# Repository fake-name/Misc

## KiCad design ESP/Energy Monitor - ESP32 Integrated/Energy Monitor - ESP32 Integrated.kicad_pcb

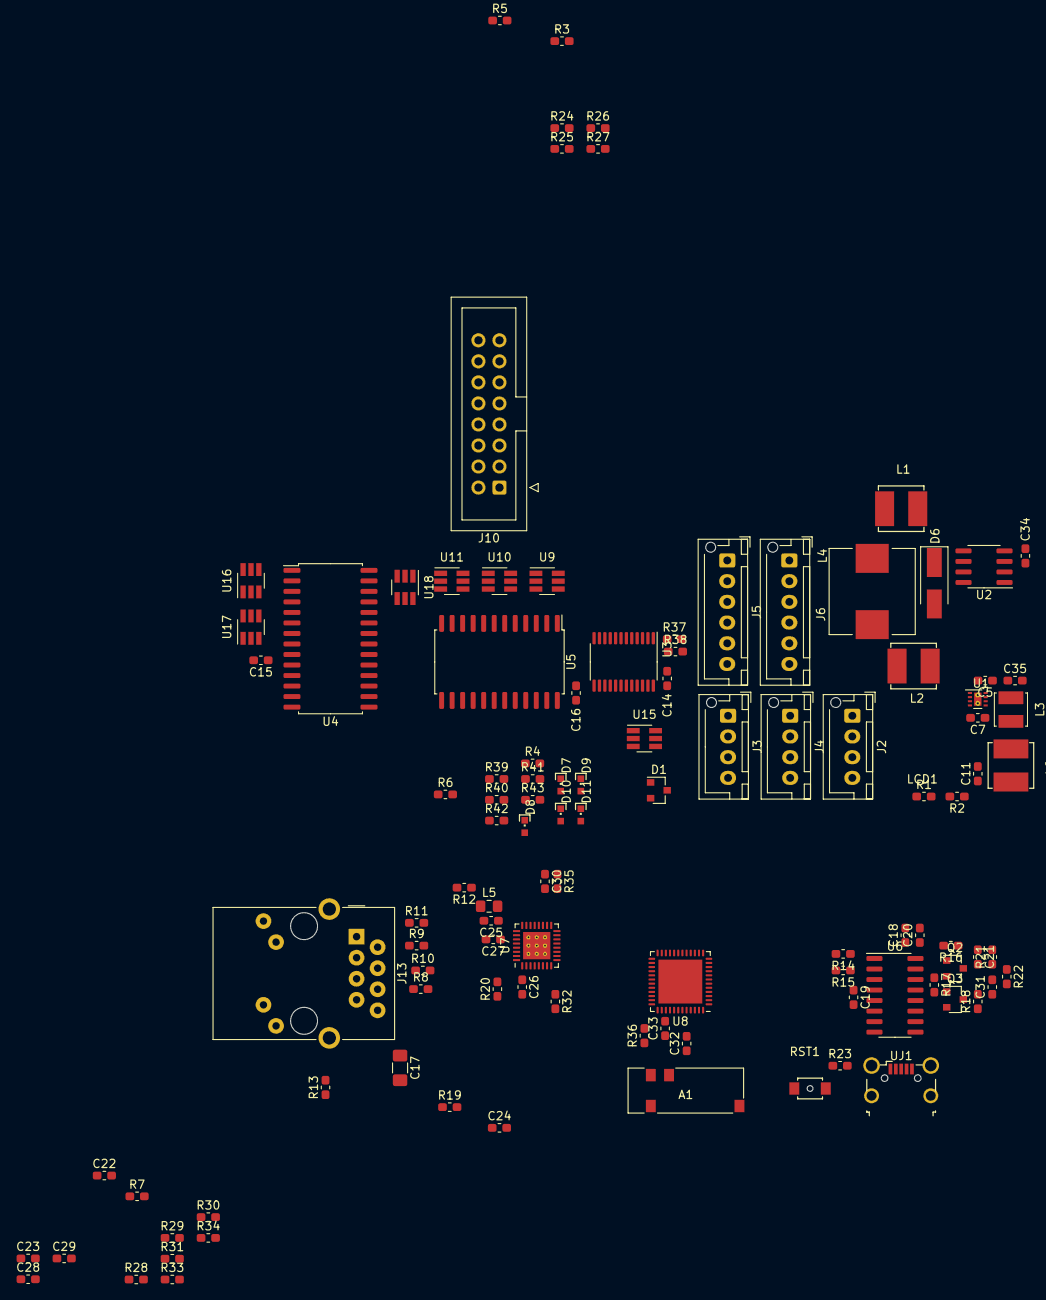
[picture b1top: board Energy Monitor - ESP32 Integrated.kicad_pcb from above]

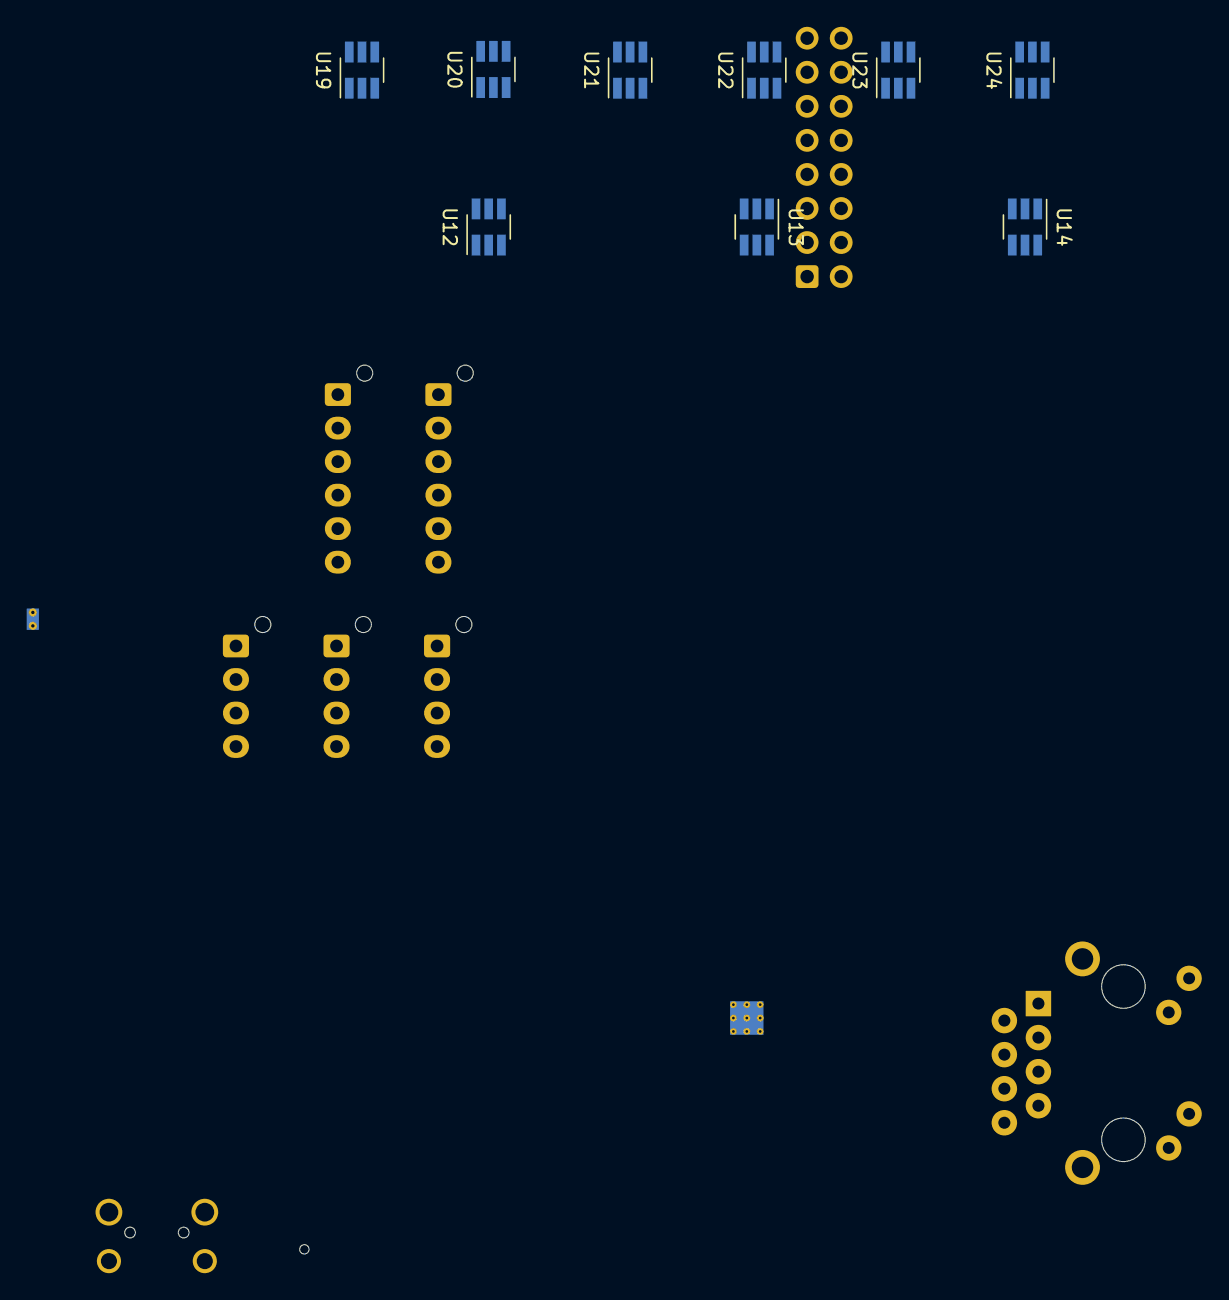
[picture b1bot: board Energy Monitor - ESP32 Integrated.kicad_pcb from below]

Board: 4 copper layers, 118 parts (9 on the bottom side), 113 nets, no tracks yet.

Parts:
A1: ProAnt_PRO-OB-440
C5, C20: 10 uF; C_0603_1608Metric_Pad1.05x0.95mm_HandSolder
C7, C11: 22 uF; C_0603_1608Metric_Pad1.05x0.95mm_HandSolder
C14, C15, C16, C18, C19, C35: 0.1 uF; C_0603_1608Metric_Pad1.05x0.95mm_HandSolder
C17: 1nF/2000V/10%/X7R/C1206; C_1206_3216Metric_Pad1.42x1.75mm_HandSolder
C21, C31, C32, C33: DNP; C_0603_1608Metric_Pad1.05x0.95mm_HandSolder
C22, C25: 22uF/6.3V/20%/X5R/C0603; C_0603_1608Metric_Pad1.05x0.95mm_HandSolder
C23: 100nF/16V/10%/X7R/C0603; C_0603_1608Metric_Pad1.05x0.95mm_HandSolder
C24, C26, C27, C29: 100nF/16V/10%/X7R/C0402; C_0603_1608Metric_Pad1.05x0.95mm_HandSolder
C28: 2.2uF/6.3V/10%/X5R/C0603; C_0603_1608Metric_Pad1.05x0.95mm_HandSolder
C30: NA(10uF/6.3V/20%/X5R/C0603); C_0603_1608Metric_Pad1.05x0.95mm_HandSolder
C34: 1 uF, 35V; C_0603_1608Metric_Pad1.05x0.95mm_HandSolder
D1: BAT54S; SOT-23
D6: SS36; D_SMA_Handsoldering
D7, D8, D9, D10, D11: LED_Small; CHIPLED_0603
J2, J3, J4: Conn_01x04; JST_XH_B4B-XH-AM_1x04_P2.50mm_Vertical
J5, J6: Conn_01x05; JST_XH_B6B-XH-AM_1x06_P2.50mm_Vertical
J10: Conn_02x08_Odd_Even; IDC-Header_2x08_P2.54mm_Vertical
J13: RJ45_Amphenol_RJMG1BD3B8K1ANR
L1, L2, L6: 15 uH; CR50x0 SMD Inductor
L3: 2.2uH; L_Murata_LQH44DN
L4: 47uH/3A; L_Wuerth_HCI-1040
L5: FB0805/600R/2A; L_0805_2012Metric_Pad1.15x1.40mm_HandSolder
LCD1: 0.96; 12864-DISP-I2C
Q2, Q3: BC817-40(SOT23); SOT-23
R1, R2, R5, R6, R19, R28, R29, R30, R31, R32, R33, R34: 2.2K; R_0603_1608Metric_Pad1.05x0.95mm_HandSolder
R3, R4, R35: 10K; R_0603_1608Metric_Pad1.05x0.95mm_HandSolder
R7: 0R(board_mounted); R_0603_1608Metric_Pad1.05x0.95mm_HandSolder
R8, R9, R10, R11: 49.9R/1%; R_0603_1608Metric_Pad1.05x0.95mm_HandSolder
R12, R13: 2.2k; R_0603_1608Metric_Pad1.05x0.95mm_HandSolder
R14, R15, R18: 220R; R_0603_1608Metric_Pad1.05x0.95mm_HandSolder
R16, R17, R21, R39, R40, R41, R42, R43: 1K; R_0603_1608Metric_Pad1.05x0.95mm_HandSolder
R20: 12.1k/1%; R_0603_1608Metric_Pad1.05x0.95mm_HandSolder
R22: DNP; R_0603_1608Metric_Pad1.05x0.95mm_HandSolder
R23: 100R; R_0603_1608Metric_Pad1.05x0.95mm_HandSolder
R24, R25, R26, R27: 4.7K; R_0603_1608Metric_Pad1.05x0.95mm_HandSolder
R36: 0R; R_0603_1608Metric_Pad1.05x0.95mm_HandSolder
R37, R38: 499K; R_0603_1608Metric_Pad1.05x0.95mm_HandSolder
RST1: IT1185AU2; K2-1823SA-A4DW-06
U1: TPS62082; WSON-8-1EP_2x2mm_P0.5mm_EP0.9x1.6mm_ThermalVias
U2: XL2001; SOIC-8_3.9x4.9mm_P1.27mm
U3: TCA9548APWR; TSSOP-24_4.4x7.8mm_P0.65mm
U4: MCP23017_SO; SOIC-28W_7.5x17.9mm_P1.27mm
U5: SOIC-24W_7.5x15.4mm_P1.27mm
U6: CH340C; SOIC-16_3.9x9.9mm_P1.27mm
U7: LAN8710A-EZC(QFN32); QFN-32-1EP_5x5mm_P0.5mm_EP3.3x3.3mm_ThermalVias
U8: ESP32-PICO-D4; QFN-48-1EP_7x7mm_P0.5mm_EP5.3x5.3mm
U9, U10, U11, U12, U13, U14, U15, U16, U17, U18, U19, U20, U21, U22, U23, U24: QUAD-ESD-DIODE; SOT-23-6_Handsoldering
UJ1: USB_B_Micro; USB_Micro-B_XKB_U254-051N-4BH806

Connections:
+3V3: C11.1, C14.1, C15.1, C16.1, C18.1, C19.1, C20.1, C22.1, C24.1, D1.2, D11.2, J2.3, J3.3, J4.3, J5.2, J6.2, J10.1, J10.5, L5.1, L6.2, R1.1, R2.1, R3.1, R4.1, R5.1, R6.1, R19.1, R21.1, R22.1, R24.1, R25.1, R26.1, R27.1, R29.1, R31.1, R33.1, R34.1, R35.1, U3.24, U4.9, U5.24, U6.4, U6.16, U7.12, U8.1, U8.3, U8.4, U8.19, U8.26, U8.37, U8.43, U8.46, U9.5, U10.5, U11.5, U12.5, U13.5, U14.5, U15.5, U16.5, U17.5, U18.5, U19.5, U20.5, U21.5, U22.5, U23.5, U24.5
+5V: C5.1, C35.1, J2.4, J3.4, J4.4, J5.1, J6.1, J10.2, L2.2, U1.1, U1.8
/COM/EXP_INT: U4.20, U8.10
/COM/EXT_SCL: R37.1, U3.22, U8.25
/COM/EXT_SCL_PT_1: J5.4, R26.2, U3.18, U15.1
/COM/EXT_SCL_PT_2: J6.4, R27.2, U3.20, U15.6
/COM/EXT_SDA: R38.1, U3.23, U8.21
/COM/EXT_SDA_PT_1: J5.3, R24.2, U3.17, U15.3
/COM/EXT_SDA_PT_2: J6.3, R25.2, U3.19, U15.4
/COM/INT_SCL: R1.2, U4.12, U8.13
/COM/INT_SDA: R2.2, U4.13, U8.12
/COM/IRQ_1: U4.1, U16.6
/COM/IRQ_2: U4.2, U16.4
/COM/IRQ_3: U4.3, U16.3
/COM/IRQ_4: U4.4, U16.1
/COM/IRQ_5: U4.5, U17.6
/COM/IRQ_6: U4.6, U17.4
/COM/IRQ_7: J10.7, U4.7, U17.3
/COM/IRQ_8: J10.9, U4.8, U17.1
/COM/IRQ_9: U4.25, U18.6
/COM/IRQ_10: U4.26, U18.4
/COM/IRQ_11: U4.27, U18.3
/COM/IRQ_12: U4.28, U18.1
/COM/SCL1: U3.5, U12.1
/COM/SCL2: U3.7, U12.4
/COM/SCL3: U3.9, U13.4
/COM/SCL4: J10.4, U3.11, U13.1
/COM/SCL5: U3.14, U14.4
/COM/SCL6: U3.16, U14.1
/COM/SDA1: U3.4, U12.6
/COM/SDA2: U3.6, U12.3
/COM/SDA3: U3.8, U13.3
/COM/SDA4: J10.3, U3.10, U13.6
/COM/SDA5: U3.13, U14.3
/COM/SDA6: U3.15, U14.6
/COM/SPI_CS_EN: R4.2, R43.2, U5.18, U8.24
/COM/SPI_MISO: J10.13, U8.11, U19.3, U20.3, U21.3, U22.3, U23.3, U24.3
/COM/SPI_MOSI: J10.11, U8.18, U19.1, U20.1, U21.1, U22.1, U23.1, U24.1
/COM/SPI_SCLK: J10.15, U8.22, U19.4, U20.4, U21.4, U22.4, U23.4, U24.4
/COM/~CS_1: U5.1, U9.6
/COM/~CS_2: U5.2, U9.4
/COM/~CS_3: U5.3, U9.3
/COM/~CS_4: U5.4, U9.1
/COM/~CS_5: U5.5, U10.6
/COM/~CS_6: U5.6, U10.4
/COM/~CS_7: J10.6, U5.7, U10.3
/COM/~CS_8: J10.8, U5.8, U10.1
/COM/~CS_9: U5.9, U11.6
/COM/~CS_10: U5.10, U11.4
/COM/~CS_11: U5.11, U11.3
/COM/~CS_12: U5.13, U11.1
/ESP32/1WIRE_IO: D1.3, J2.2, J3.2, J4.2, R3.2, U8.17
/ESP32/ESP_EN: C21.1, Q2.3, R21.2, RST1.1, U8.9
/ESP32/GPIO0: C31.1, R18.2, R22.2, U8.23
/ESP32/GPIO1/U0TXD: R15.2, U8.41
/ESP32/GPIO3/U0RXD: R14.2, U8.40
/ESP32/GPIO17/EMAC_CLK_OUT_180: U7.5, U8.27
/ESP32/GPIO18/MDIO(RMII): R33.2, U7.16, U8.35
/ESP32/GPIO19/EMAC_TXD0(RMII): U7.22, U8.38
/ESP32/GPIO21/EMAC_TX_EN(RMII): U7.21, U8.42
/ESP32/GPIO22/EMAC_TXD1(RMII): U7.23, U8.39
/ESP32/GPIO23/MDC(RMII): U7.17, U8.36
/ESP32/GPIO25/EMAC_RXD0(RMII): R29.2, U7.11, U8.14
/ESP32/GPIO26/EMAC_RXD1(RMII): R19.2, U7.10, U8.15
/ESP32/GPIO27/EMAC_RX_CRS_DV: R34.2, U7.15, U8.16
/ESP32/PHY_CT: C23.1, J13.R4, J13.R5, R7.2
/ESP32/PHY_VDDA: C25.1, C26.1, C27.1, L5.2, R7.1, R8.1, R9.1, R10.1, R11.1, R12.1, U7.1, U7.27
/ESP32/PHY_VDDCR: C28.1, C29.1, U7.6
/ESP32/RXN: J13.R6, R8.2, U7.30
/ESP32/RXP: J13.R3, R9.2, U7.31
/ESP32/TXN: J13.R2, R10.2, U7.28
/ESP32/TXP: J13.R1, R11.2, U7.29
GND: A1.1, C5.2, C7.2, C11.2, C14.2, C15.2, C16.2, C17.2, C18.2, C19.2, C20.2, C21.2, C22.2, C23.2, C24.2, C25.2, C26.2, C27.2, C28.2, C29.2, C30.1, C31.2, C32.2, C33.2, C35.2, D1.1, D6.2, D7.1, D8.1, D9.1, D10.1, J2.1, J3.1, J4.1, J5.5, J6.5, J10.10, J10.12, J10.14, J10.16, J13.R8, R13.1, R20.1, R23.1, R28.2, R30.2, R32.2, R37.2, R38.2, RST1.2, U1.2, U1.3, U1.9, U2.7, U2.8, U3.12, U4.10, U4.15, U4.16, U4.17, U5.12, U5.19, U6.1, U7.24, U7.25, U8.49, U9.2, U10.2, U11.2, U12.2, U13.2, U14.2, U15.2, U16.2, U17.2, U18.2, U19.2, U20.2, U21.2, U22.2, U23.2, U24.2, UJ1.5
unnamed: A1.2, C32.1, R36.1
unnamed: C34.1, L1.2, U2.4
unnamed: L2.1, L4.2, U2.1
unnamed: C7.1, L3.2, L6.1, U1.5
unnamed: C17.1, J13.13
unnamed: C30.2, R35.2, U7.19
unnamed: C33.1, R36.2, U8.2
unnamed: C34.2, U2.3
unnamed: D6.1, L4.1, U2.5, U2.6
unnamed: D7.2, R39.2
unnamed: D8.2, R40.2
unnamed: D9.2, R41.2
unnamed: D10.2, R42.2
unnamed: D11.1, R43.1
unnamed: J13.L1, U7.3
unnamed: J13.L2, R13.2
unnamed: J13.L3, U7.2
unnamed: J13.L4, R12.2
unnamed: L3.1, U1.7
unnamed: Q2.1, R16.2
unnamed: Q2.2, R17.1, U6.14
unnamed: Q3.1, R17.2
unnamed: Q3.2, R16.1, U6.13
unnamed: Q3.3, R18.1
unnamed: R5.2, U3.3
unnamed: R6.2, U4.18
unnamed: R14.1, U6.2
unnamed: R15.1, U6.3
unnamed: R20.2, U7.32
unnamed: R23.2, UJ1.6
unnamed: R28.1, U7.13
unnamed: R30.1, U7.7
unnamed: R31.2, U7.9
unnamed: R32.1, U7.8
unnamed: R39.1, U3.21, U4.24, U5.20
unnamed: R40.1, U3.2, U4.23, U5.21
unnamed: R41.1, U3.1, U4.22, U5.22
unnamed: R42.1, U4.21, U5.23
unnamed: U6.5, UJ1.3
unnamed: U6.6, UJ1.2

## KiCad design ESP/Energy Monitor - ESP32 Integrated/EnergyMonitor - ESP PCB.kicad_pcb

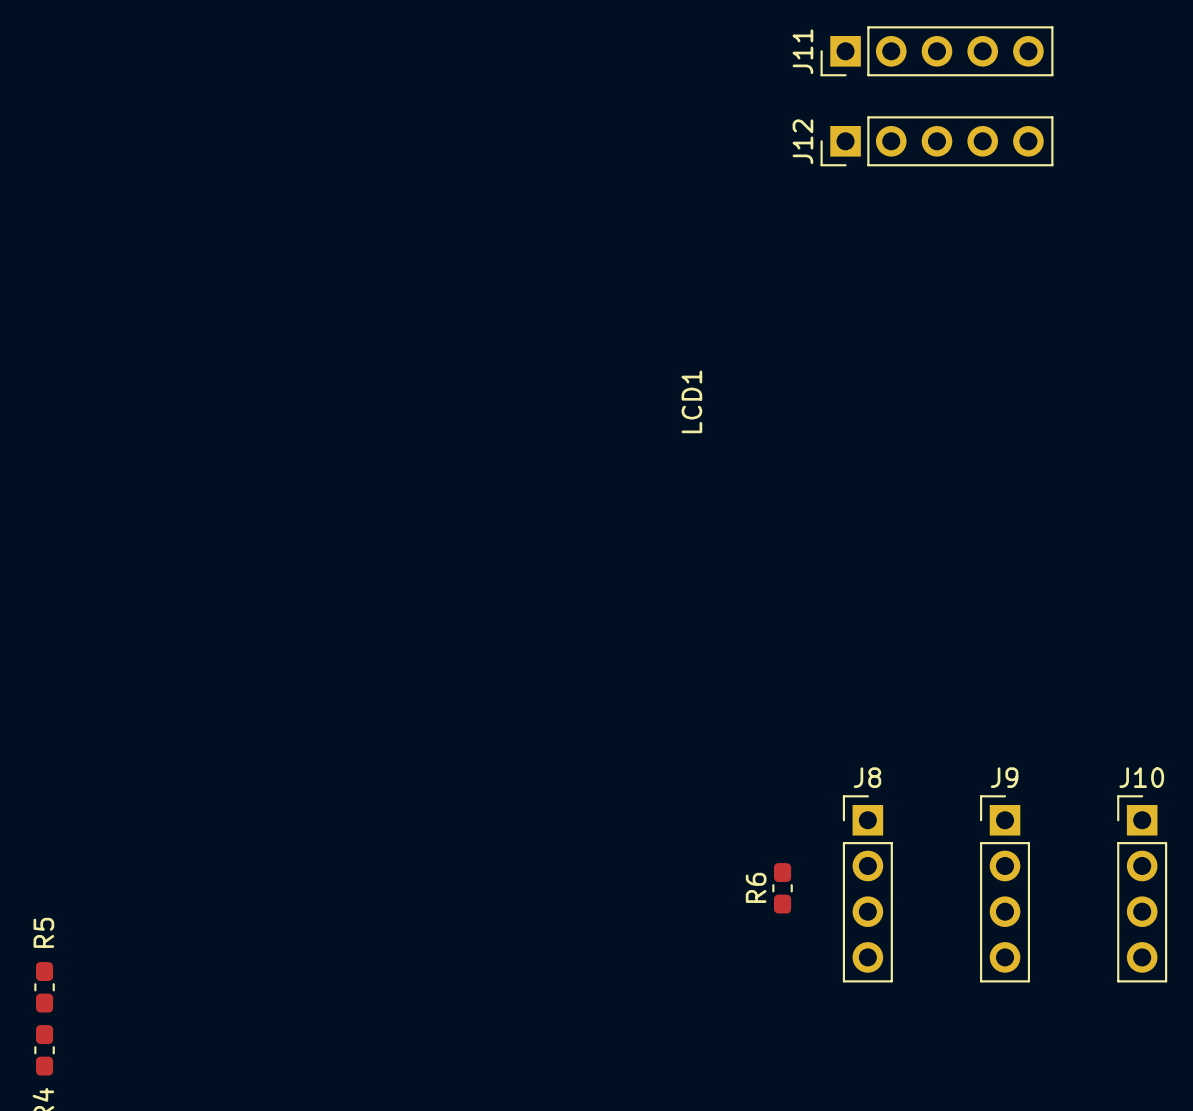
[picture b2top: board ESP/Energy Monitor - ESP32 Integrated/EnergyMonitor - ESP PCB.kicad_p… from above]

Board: 4 copper layers, 9 parts (0 on the bottom side), 6 nets, no tracks yet.

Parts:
J8, J9, J10: Conn_01x04; PinHeader_1x04_P2.54mm_Vertical
J11, J12: Conn_01x05; PinHeader_1x05_P2.54mm_Vertical
LCD1: 0.96; 12864-DISP-I2C
R4, R5: 2.2K; R_0603_1608Metric_Pad1.05x0.95mm_HandSolder
R6: 10K; R_0603_1608Metric_Pad1.05x0.95mm_HandSolder

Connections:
+3V3: J8.3, J9.3, J10.3, J11.2, J12.2, R4.1, R5.1, R6.1
+5V: J8.4, J9.4, J10.4, J11.1, J12.1
GND: J8.1, J9.1, J10.1, J11.5, J12.5
unnamed: J8.2, J9.2, J10.2, R6.2
unnamed: J11.3, J12.3, R5.2
unnamed: J11.4, J12.4, R4.2

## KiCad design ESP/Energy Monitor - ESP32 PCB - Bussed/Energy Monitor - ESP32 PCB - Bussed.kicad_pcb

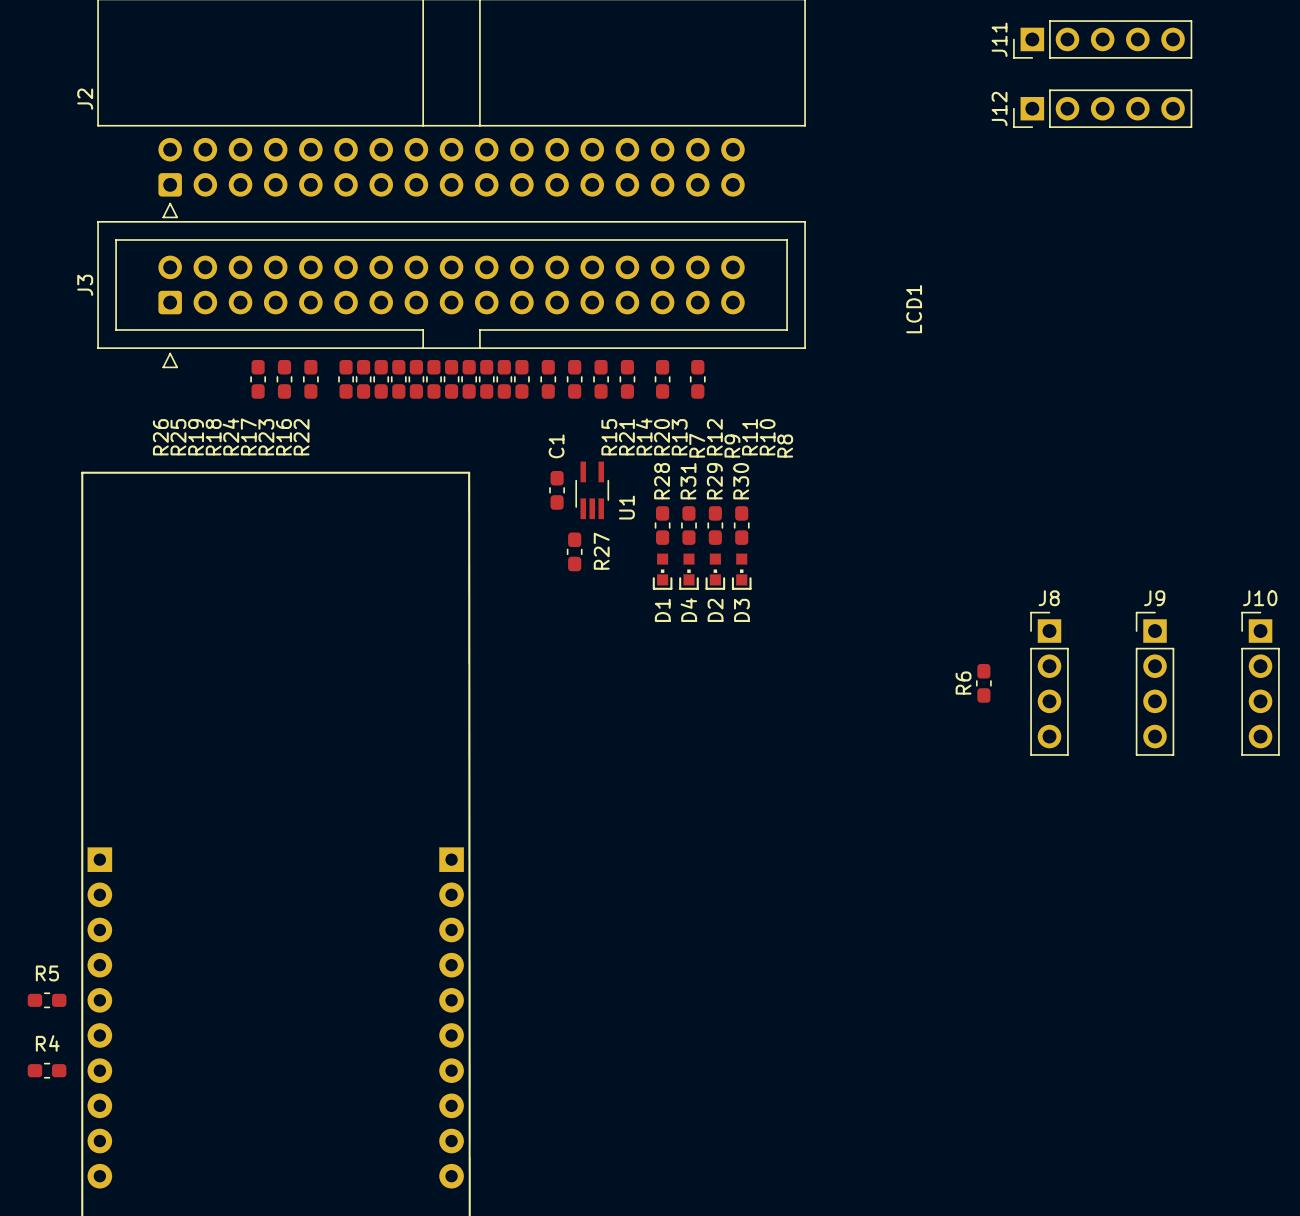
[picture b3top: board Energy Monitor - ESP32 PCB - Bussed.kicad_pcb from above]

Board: 4 copper layers, 43 parts (0 on the bottom side), 32 nets, no tracks yet.

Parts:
C1: 0.1 uF; C_0603_1608Metric_Pad1.05x0.95mm_HandSolder
D1, D2, D3, D4: LED; CHIPLED_0603
J2: Conn_02x17_Odd_Even; IDC-Header_2x17_P2.54mm_Horizontal
J3: Conn_02x17_Odd_Even; IDC-Header_2x17_P2.54mm_Vertical
J8, J9, J10: Conn_01x04; PinHeader_1x04_P2.54mm_Vertical
J11, J12: Conn_01x05; PinHeader_1x05_P2.54mm_Vertical
LCD1: 0.96; 12864-DISP-I2C
R4, R5: 2.2K; R_0603_1608Metric_Pad1.05x0.95mm_HandSolder
R6, R27: 10K; R_0603_1608Metric_Pad1.05x0.95mm_HandSolder
R7, R9, R12: 660R; R_0603_1608Metric_Pad1.05x0.95mm_HandSolder
R8, R10, R11: 49.9K; R_0603_1608Metric_Pad1.05x0.95mm_HandSolder
R13, R14, R15, R16, R17, R18, R19, R20, R21, R22, R23, R24, R25, R26: 100R; R_0603_1608Metric_Pad1.05x0.95mm_HandSolder
R28, R29, R30, R31: 1K; R_0603_1608Metric_Pad1.05x0.95mm_HandSolder
U1: 74LVC1G04; SOT-353_SC-70-5_Handsoldering
U2: ESP32-POE Module; ESP32-POE

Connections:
+3V3: C1.1, J2.1, J2.3, J2.5, J2.7, J3.1, J3.3, J3.5, J3.7, J8.3, J9.3, J10.3, J11.2, J12.2, R4.1, R5.1, R6.1, R7.1, R9.1, R28.1, R31.1, U1.5
+5V: J2.2, J2.4, J2.6, J3.2, J3.4, J3.6, J8.4, J9.4, J10.4, J11.1, J12.1, R30.1, U2.1
/ESP1/IRQ_1: J2.23, J3.23, R7.2
/ESP1/IRQ_2: J2.25, J3.25, R9.2
/ESP1/MISO: J2.29, J3.29, R10.1, U2.13
/ESP1/MOSI: J2.27, J3.27, R11.1, U2.18
/ESP1/RESET: J2.22, J3.22, R12.1
/ESP1/SCL: J11.3, J12.3, R5.2, U2.5
/ESP1/SCLK: J2.31, J3.31, R8.1, U2.19
/ESP1/SDA: J11.4, J12.4, R4.2, U2.7
/ESP1/~CS_1: J2.8, J3.8, R26.2
/ESP1/~CS_2: J2.9, J3.9, R19.2
/ESP1/~CS_3: J2.10, J3.10, R25.2
/ESP1/~CS_4: J2.11, J3.11, R18.2
/ESP1/~CS_5: J2.12, J3.12, R24.2
/ESP1/~CS_6: J2.13, J3.13, R17.2
/ESP1/~CS_7: J2.14, J3.14, R23.2
/ESP1/~CS_8: J2.15, J3.15, R16.2
/ESP1/~CS_9: J2.16, J3.16, R22.2
/ESP1/~CS_10: J2.17, J3.17, R15.2
/ESP1/~CS_11: J2.18, J3.18, R21.2
/ESP1/~CS_12: J2.19, J3.19, R14.2
/ESP1/~CS_13: J2.20, J3.20, R20.2
/ESP1/~CS_14: J2.21, J3.21, R13.2
GND: C1.2, D2.1, D3.1, D4.1, J2.24, J2.26, J2.28, J2.30, J2.32, J2.33, J2.34, J3.24, J3.26, J3.28, J3.30, J3.32, J3.33, J3.34, J8.1, J9.1, J10.1, J11.5, J12.5, R8.2, R10.2, R11.2, R27.2, U1.3, U2.3
unnamed: D1.2, R28.2
unnamed: D2.2, R29.2
unnamed: D3.2, R30.2
unnamed: D4.2, R31.2
unnamed: J8.2, J9.2, J10.2, R6.2, U2.15
unnamed: R12.2, R29.1, U1.4
unnamed: R27.1, U1.2

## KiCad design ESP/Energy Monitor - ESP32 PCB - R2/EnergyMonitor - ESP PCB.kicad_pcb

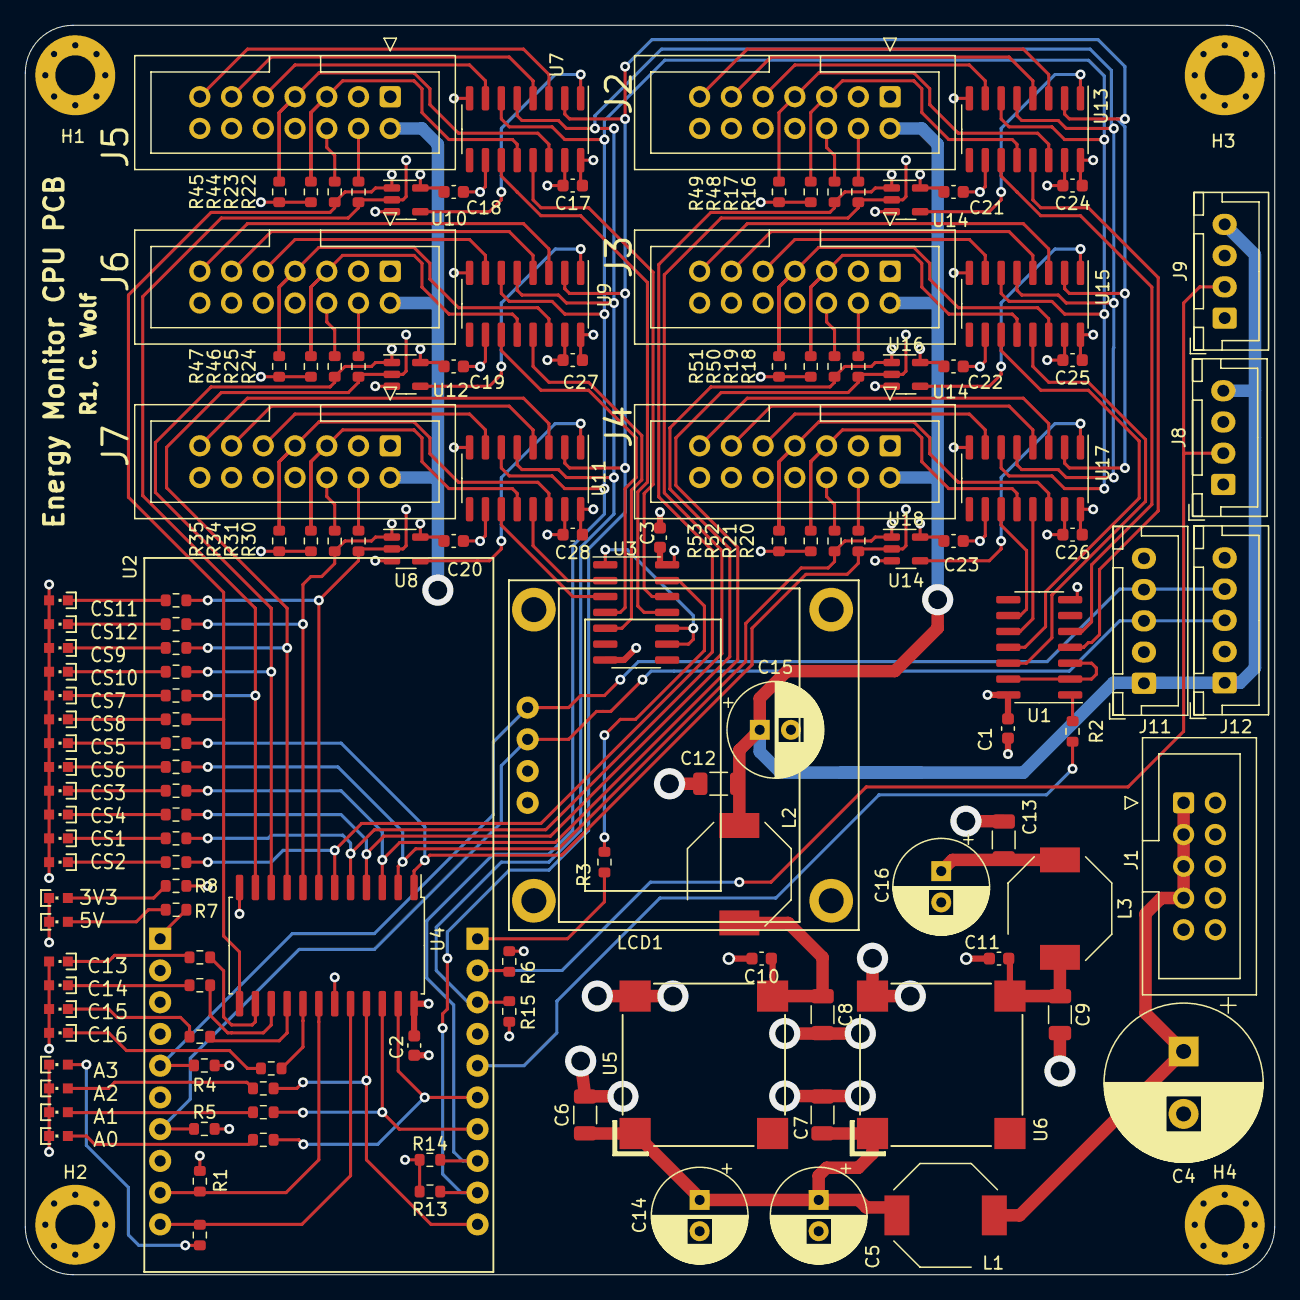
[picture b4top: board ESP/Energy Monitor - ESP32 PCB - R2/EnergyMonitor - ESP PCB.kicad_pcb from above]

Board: 4 copper layers, 100.0 x 100.0 mm, 142 parts (0 on the bottom side), 122 nets.

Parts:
C1, C2, C3, C10, C11, C17, C18, C19, C20, C21, C22, C23, C24, C25, C26, C27, C28: 0.1 uF; C_0603_1608Metric
C4: CP1; CP_Radial_D12.5mm_P5.00mm
C5, C14, C15, C16: CP1; CP_Radial_D7.5mm_P2.50mm
C6, C7: 10 uF, 35V; C_1206_3216Metric
C8, C9, C12, C13: 22 uF; C_1206_3216Metric
D1, D2, D3, D4, D5, D6, D7, D8, D9, D10, D11, D12, D13, D14, D15, D16, D17, D18, D19, D20, D21, D22: LED; CHIPLED_0603
H1, H2, H3, H4: MountingHole; MountingHole_3.2mm_M3_Pad_Via
J1: Conn_02x05_Odd_Even; IDC-Header_2x05_P2.54mm_Vertical
J2, J3, J4, J5, J6, J7: Conn_02x07_Odd_Even; IDC-Header_2x07_P2.54mm_Vertical
J8, J9: Conn_01x04; JST_XH_B4B-XH-A_1x04_P2.50mm_Vertical
J11, J12: Conn_01x05; JST_XH_B5B-XH-A_1x05_P2.50mm_Vertical
L1, L2, L3: 47 uH; L_Bourns-SRU8028_8.0x8.0mm
LCD1: 0.96"-SSD1306-DISP-I2C; 12864-DISP-I2C
R1, R6, R13, R14, R15: 10K; R_0603_1608Metric
R2, R3: 330R; R_0603_1608Metric
R4, R5: 2.2K; R_0603_1608Metric
R7, R8, R9, R10, R11, R12, R26, R27, R28, R29, R32, R33, R36, R37, R38, R39, R40, R41, R42, R43, R54, R55: 1K; R_0603_1608Metric
R16, R17, R18, R19, R20, R21, R22, R23, R24, R25, R30, R31: 100R; R_0603_1608Metric
R34, R35, R44, R45, R46, R47, R48, R49, R50, R51, R52, R53: 22K; R_0603_1608Metric
U1, U3: 4072; SOIC-14_3.9x8.7mm_P1.27mm
U2: ESP32-POE Module; ESP32-POE
U4: 74HC154; SOIC-24W_7.5x15.4mm_P1.27mm
U5: VXO7805-500-M; VXO78x-500-M
U6: VXO7803-500-M; VXO78x-500-M
U7, U9, U11, U13, U15, U17: 74LS367; SOIC-16_3.9x9.9mm_P1.27mm
U8, U10, U12, U14, U16, U18: 74AHC1G08; SOT-23-5

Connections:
+3.3V: C1.1, C2.1, C3.1, C13.1, C16.1, C17.1, C18.1, C19.1, C20.1, C21.1, C22.1, C23.1, C24.1, C25.1, C26.1, C27.1, C28.1, D7.2 (A), D8.2 (A), D9.2 (A), D10.2 (A), D11.2 (A), D12.2 (A), D13.2 (A), D14.2 (A), D15.2 (A), D16.2 (A), D17.2 (A), D18.2 (A), D19.2 (A), D20.2 (A), D21.2 (A), D22.2 (A), J2.1, J2.3, J3.1, J3.3, J4.1, J4.3, J5.1, J5.3, J6.1, J6.3, J7.1, J7.3, J8.3, J9.3, J11.2, J12.2, L3.2, R1.1, R4.1, R5.1, R6.1, R8.1, U1.14 (VDD), U3.14 (VDD), U4.24 (VCC), U7.16 (VCC), U8.5 (V), U9.16 (VCC), U10.5 (V), U11.16 (VCC), U12.5 (V), U13.16 (VCC), U14.5 (V), U15.16 (VCC), U16.5 (V), U17.16 (VCC), U18.5 (V)
+5V: C12.1, C15.1, J2.2, J3.2, J4.2, J5.2, J6.2, J7.2, J8.4, J9.4, J11.1, J12.1, L2.2, LCD1.1 (VCC), R7.1, U2.1 (5V)
+9V: C4.1, J1.1, J1.3, J1.5, J1.7, L1.1
/ESP1/1WIRE: J8.2, J9.2, R6.2, U2.12 (GPIO36/U1RXD)
/ESP1/C13: R40.2, U4.14 (S12)
/ESP1/C14: R41.2, U4.15 (S13)
/ESP1/C15: R42.2, U4.16 (S14)
/ESP1/C16: R43.2, U4.17 (S15)
/ESP1/CS_A0: R26.1, U2.16 (GPIO32), U4.23 (A0)
/ESP1/CS_A1: R27.1, U2.17 (GPIO16/I2C-SCL), U4.22 (A1)
/ESP1/CS_A2: R28.1, U2.20 (GPIO13/I2C-SDA), U4.21 (A2)
/ESP1/CS_A3: R29.1, U2.10 (GPIO5/SPI_CS), U4.20 (A3)
/ESP1/CS_EN: R1.2, U2.9 (GPIO4/U1TXD), U4.18 (E0)
/ESP1/I2C_SCL: J11.3, J12.3, LCD1.3 (SCL), R5.2, U2.7 (GPIO2/HS2_DATA0)
/ESP1/I2C_SDA: J11.4, J12.4, LCD1.4 (SDA), R4.2, U2.5 (GPIO0)
/ESP1/IRQ_1: J2.5, R48.1, U13.12 (I5)
/ESP1/IRQ_2: J2.7, R49.1, U13.14 (I6)
/ESP1/IRQ_3: J3.5, R50.1, U15.12 (I5)
/ESP1/IRQ_4: J3.7, R51.1, U15.14 (I6)
/ESP1/IRQ_5: J4.5, R52.1, U17.12 (I5)
/ESP1/IRQ_6: J4.7, R53.1, U17.14 (I6)
/ESP1/IRQ_7: J5.5, R44.1, U7.12 (I5)
/ESP1/IRQ_8: J5.7, R45.1, U7.14 (I6)
/ESP1/IRQ_9: J6.5, R46.1, U9.12 (I5)
/ESP1/IRQ_10: J6.7, R47.1, U9.14 (I6)
/ESP1/IRQ_11: J7.5, R34.1, U11.12 (I5)
/ESP1/IRQ_12: J7.7, R35.1, U11.14 (I6)
/ESP1/MISO: R15.1, U2.13 (GPIO35), U7.5 (O2a), U9.5 (O2a), U11.5 (O2a), U13.5 (O2a), U15.5 (O2a), U17.5 (O2a)
/ESP1/MISO_1: J2.11, U13.4 (I2)
/ESP1/MISO_2: J3.11, U15.4 (I2)
/ESP1/MISO_3: J4.11, U17.4 (I2)
/ESP1/MISO_4: J5.11, U7.4 (I2)
/ESP1/MISO_5: J6.11, U9.4 (I2)
/ESP1/MISO_6: J7.11, U11.4 (I2)
/ESP1/MOSI: R14.1, U2.18 (GPIO15/HS2_CMD), U7.6 (I3), U9.6 (I3), U11.6 (I3), U13.6 (I3), U15.6 (I3), U17.6 (I3)
/ESP1/MOSI_1: J2.9, U13.7 (O3a)
/ESP1/MOSI_2: J3.9, U15.7 (O3a)
/ESP1/MOSI_3: J4.9, U17.7 (O3a)
/ESP1/MOSI_4: J5.9, U7.7 (O3a)
/ESP1/MOSI_5: J6.9, U9.7 (O3a)
/ESP1/MOSI_6: J7.9, U11.7 (O3a)
/ESP1/SCLK: R13.1, U2.19 (GPIO14/HS2_CLK), U7.2 (I1), U9.2 (I1), U11.2 (I1), U13.2 (I1), U15.2 (I1), U17.2 (I1)
/ESP1/SCLK_1: J2.13, U13.3 (O1a)
/ESP1/SCLK_2: J3.13, U15.3 (O1a)
/ESP1/SCLK_3: J4.13, U17.3 (O1a)
/ESP1/SCLK_4: J5.13, U7.3 (O1a)
/ESP1/SCLK_5: J6.13, U9.3 (O1a)
/ESP1/SCLK_6: J7.13, U11.3 (O1a)
/ESP1/~CS_1_R: R16.1, R32.2, U4.5 (S4), U14.2
/ESP1/~CS_1: J2.4, R16.2
/ESP1/~CS_2_R: R17.1, R33.2, U4.6 (S5), U14.1
/ESP1/~CS_2: J2.6, R17.2
/ESP1/~CS_3_R: R11.2, R18.1, U4.3 (S2), U16.2
/ESP1/~CS_3: J3.4, R18.2
/ESP1/~CS_4_R: R12.2, R19.1, U4.4 (S3), U16.1
/ESP1/~CS_4: J3.6, R19.2
/ESP1/~CS_5_R: R9.2, R20.1, U4.1 (S0), U18.2
/ESP1/~CS_5: J4.4, R20.2
/ESP1/~CS_6_R: R10.2, R21.1, U4.2 (S1), U18.1
/ESP1/~CS_6: J4.6, R21.2
/ESP1/~CS_7_R: R22.1, R54.2, U4.11 (S10), U10.2
/ESP1/~CS_7: J5.4, R22.2
/ESP1/~CS_8_R: R23.1, R55.2, U4.13 (S11), U10.1
/ESP1/~CS_8: J5.6, R23.2
/ESP1/~CS_9_R: R24.1, R38.2, U4.9 (S8), U12.2
/ESP1/~CS_9: J6.4, R24.2
/ESP1/~CS_10_R: R25.1, R39.2, U4.10 (S9), U12.1
/ESP1/~CS_10: J6.6, R25.2
/ESP1/~CS_11_R: R30.1, R36.2, U4.7 (S6), U8.2
/ESP1/~CS_11: J7.4, R30.2
/ESP1/~CS_12_R: R31.1, R37.2, U4.8 (S7), U8.1
/ESP1/~CS_12: J7.6, R31.2
GND: C1.2, C2.2, C3.2, C4.2, C5.2, C6.2, C7.2, C8.2, C9.2, C10.2, C11.2, C12.2, C13.2, C14.2, C15.2, C16.2, C17.2, C18.2, C19.2, C20.2, C21.2, C22.2, C23.2, C24.2, C25.2, C26.2, C27.2, C28.2, D1.1 (K), D2.1 (K), D3.1 (K), D4.1 (K), D5.1 (K), D6.1 (K), J1.4, J1.6, J1.8, J1.10, J2.8, J2.10, J2.12, J2.14, J3.8, J3.10, J3.12, J3.14, J4.8, J4.10, J4.12, J4.14, J5.8, J5.10, J5.12, J5.14, J6.8, J6.10, J6.12, J6.14, J7.8, J7.10, J7.12, J7.14, J8.1, J9.1, J11.5, J12.5, LCD1.2 (Gnd), R13.2, R14.2, R15.2, R34.2, R35.2, R44.2, R45.2, R46.2, R47.2, R48.2, R49.2, R50.2, R51.2, R52.2, R53.2, U1.7 (VSS), U2.3 (GND), U3.7 (VSS), U4.12 (GND), U4.19 (E1), U5.2 (Gnd), U6.2 (Gnd), U7.8 (GND), U7.10 (I4), U7.15 (OEb), U8.3 (G), U9.8 (GND), U9.10 (I4), U9.15 (OEb), U10.3 (G), U11.8 (GND), U11.10 (I4), U11.15 (OEb), U12.3 (G), U13.8 (GND), U13.10 (I4), U13.15 (OEb), U14.3 (G), U15.8 (GND), U15.10 (I4), U15.15 (OEb), U16.3 (G), U17.8 (GND), U17.10 (I4), U17.15 (OEb), U18.3 (G)
unnamed: D1.2 (A), R7.2
unnamed: D2.2 (A), R8.2
unnamed: D3.2 (A), R26.2
unnamed: D4.2 (A), R27.2
unnamed: D5.2 (A), R28.2
unnamed: D6.2 (A), R29.2
unnamed: D7.1 (K), R40.1
unnamed: D8.1 (K), R41.1
unnamed: D9.1 (K), R42.1
unnamed: D10.1 (K), R43.1
unnamed: D11.1 (K), R9.1
unnamed: D12.1 (K), R10.1
unnamed: D13.1 (K), R11.1
unnamed: D14.1 (K), R12.1
unnamed: D15.1 (K), R32.1
unnamed: D16.1 (K), R33.1
unnamed: D17.1 (K), R36.1
unnamed: D18.1 (K), R37.1
unnamed: D19.1 (K), R38.1
unnamed: D20.1 (K), R39.1
unnamed: D21.1 (K), R54.1
unnamed: D22.1 (K), R55.1
unnamed: R2.2, U1.1
unnamed: R3.2, U3.13
unnamed: U1.2, U1.3, U1.13
unnamed: R2.1, U2.15 (GPIO33)
unnamed: R3.1, U2.11 (GPIO39)
unnamed: U3.1, U3.9, U3.10
unnamed: C5.1, C6.1, C7.1, C14.1, L1.2, U5.1 (+VIn), U6.1 (+VIn)
unnamed: C8.1, C10.1, L2.1, U5.3 (+VOut)
unnamed: C9.1, C11.1, L3.1, U6.3 (+VOut)
unnamed: U3.11, U7.11 (O5b)
unnamed: U3.12, U7.13 (O6b)
unnamed: U7.1 (OEa), U10.4
unnamed: U3.4, U9.11 (O5b)
unnamed: U3.5, U9.13 (O6b)
unnamed: U9.1 (OEa), U12.4
unnamed: U3.3, U11.11 (O5b)
unnamed: U3.2, U11.13 (O6b)
unnamed: U8.4, U11.1 (OEa)
unnamed: U1.5, U13.11 (O5b)
unnamed: U1.4, U13.13 (O6b)
unnamed: U13.1 (OEa), U14.4
unnamed: U1.11, U15.11 (O5b)
unnamed: U1.12, U15.13 (O6b)
unnamed: U15.1 (OEa), U16.4
unnamed: U1.9, U17.11 (O5b)
unnamed: U1.10, U17.13 (O6b)
unnamed: U17.1 (OEa), U18.4

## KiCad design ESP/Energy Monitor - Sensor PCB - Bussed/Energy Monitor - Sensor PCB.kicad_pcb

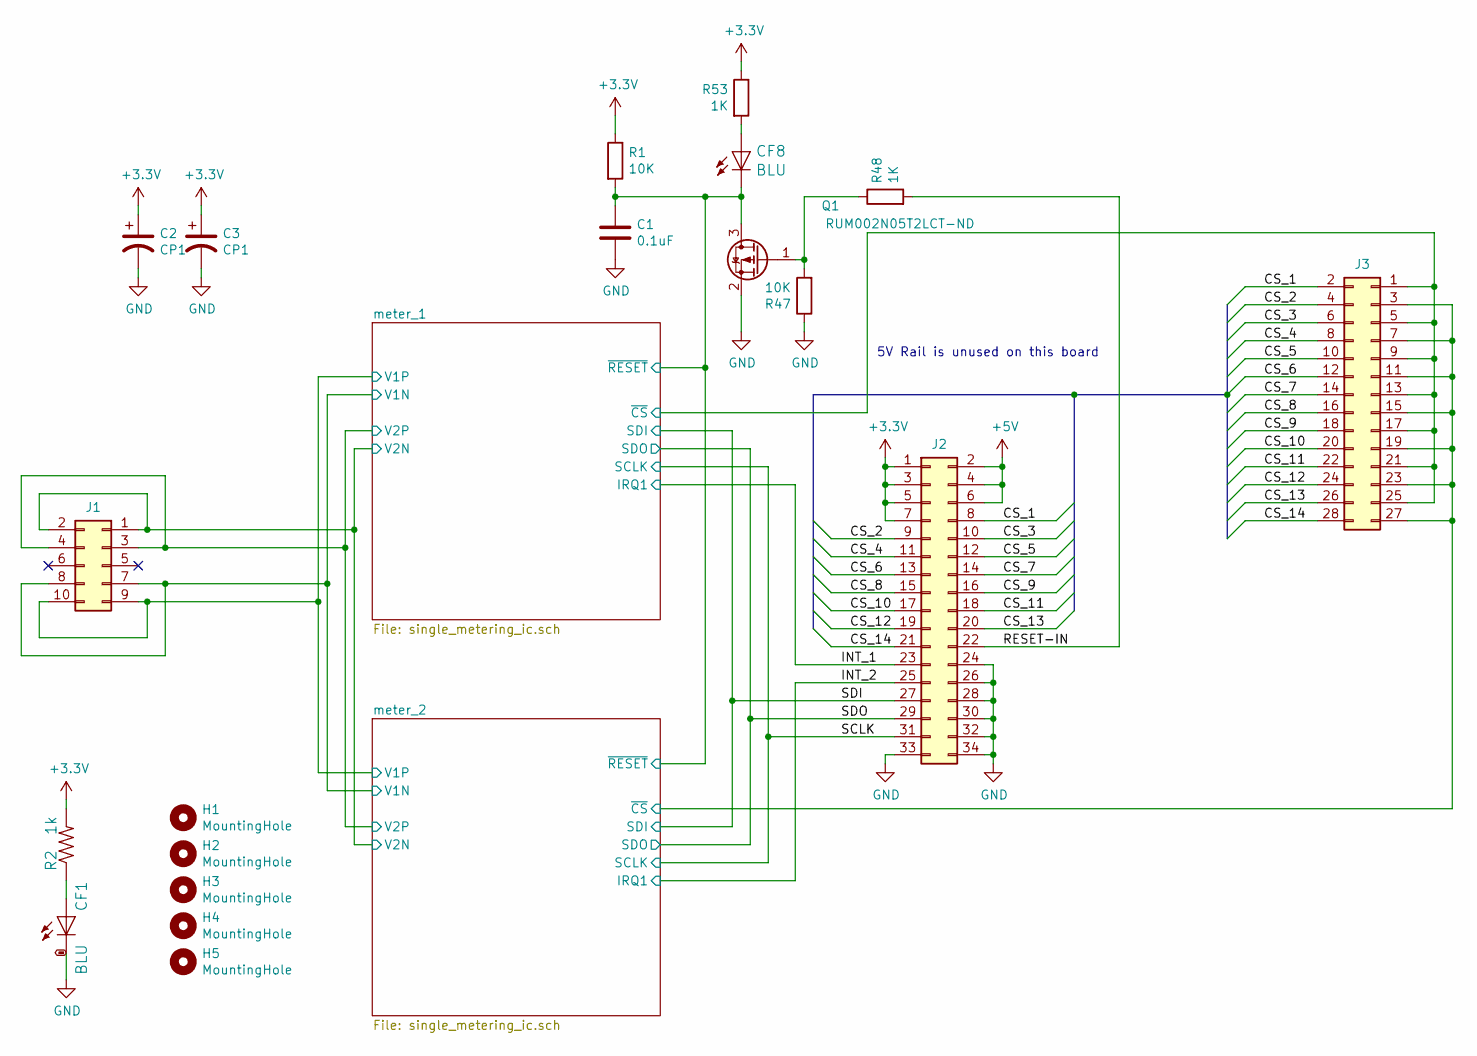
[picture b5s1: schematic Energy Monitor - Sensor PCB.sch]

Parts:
C1: 0.1uF; C_0603_1608Metric_Pad1.05x0.95mm_HandSolder
C2, C3: CP1; CP_Radial_D12.5mm_P5.00mm
CF1, CF8: BLU; CHIPLED_0603
H1, H2, H3, H4, H5: MountingHole; MountingHole_3.2mm_M3_Pad_Via
J1: Conn_02x05_Odd_Even; IDC-Header_2x05_P2.54mm_Horizontal
J2: Conn_02x17_Odd_Even; IDC-Header_2x17_P2.54mm_Horizontal
J3: Conn_02x14_Odd_Even; PinHeader_2x14_P2.54mm_Vertical
Q1: RUM002N05T2LCT-ND; SOT-723
R1, R47: 10K; R_0603_1608Metric_Pad1.05x0.95mm_HandSolder
R2: 1k; R_0603_1608Metric_Pad1.05x0.95mm_HandSolder
R48, R53: 1K; R_0603_1608Metric_Pad1.05x0.95mm_HandSolder

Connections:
+3V3: C2.1, C3.1, J2.1, J2.3, J2.5, J2.7, R1.1, R2.2, R53.1; also elsewhere on the board
+5V: J2.2, J2.4, J2.6
/CS_1: J2.8, J3.2
/CS_2: J2.9, J3.4
/CS_3: J2.10, J3.6
/CS_4: J2.11, J3.8
/CS_5: J2.12, J3.10
/CS_6: J2.13, J3.12
/CS_7: J2.14, J3.14
/CS_8: J2.15, J3.16
/CS_9: J2.16, J3.18
/CS_10: J2.17, J3.20
/CS_11: J2.18, J3.22
/CS_12: J2.19, J3.24
/CS_13: J2.20, J3.26
/CS_14: J2.21, J3.28
/INT_1: J2.23; also elsewhere on the board
/INT_2: J2.25; also elsewhere on the board
/RESET-IN: J2.22, R48.2
/meter_1/SCLK: J2.31; also elsewhere on the board
/meter_1/SDI: J2.27; also elsewhere on the board
/meter_1/SDO: J2.29; also elsewhere on the board
/meter_1/V1N: J1.7, J1.8; also elsewhere on the board
/meter_1/V1P: J1.9, J1.10; also elsewhere on the board
/meter_1/V2N: J1.1, J1.2; also elsewhere on the board
/meter_1/V2P: J1.3, J1.4; also elsewhere on the board
/meter_1/~CS: J3.1, J3.5, J3.9, J3.13, J3.17, J3.21, J3.25; also elsewhere on the board
/meter_1/~RESET: C1.1, CF8.C, Q1.3 (D), R1.2; also elsewhere on the board
/meter_2/~CS: J3.3, J3.7, J3.11, J3.15, J3.19, J3.23, J3.27; also elsewhere on the board
GND: C1.2, C2.2, C3.2, CF1.C, J2.24, J2.26, J2.28, J2.30, J2.32, J2.33, J2.34, Q1.2 (S), R47.1; also elsewhere on the board
unnamed: CF1.A, R2.1
unnamed: CF8.A, R53.2
unnamed: Q1.1 (G), R47.2, R48.1

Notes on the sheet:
5V Rail is unused on this board
